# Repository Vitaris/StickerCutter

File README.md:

# StickerCutter Conversion Project

Converting a large format printer to cut stickers

Project Overview

This project aims to repurpose a non-functional large format printer into a sticker cutting machine. The system will be controlled by a Raspberry Pi Pico rp2040 microcontroller board. An optical sensor on the former print head will detect marks around printed stickers, and a blade on the print head, which originally cut the print job after completion, will now cut strips of stickers. The project is written in C and will be released as open source on GitHub.

## Features

- **Mechanical Modifications:** The printer's existing printing head will be adapted to function as a sticker cutting head. This will involve adding an optical sensor to detect markers around printed stickers.
  
- **Software Control:** The Raspberry Pico rp2040 will control the cutting process. The software will interpret the signals from the optical sensor and instruct the cutting blade accordingly.
  
- **Language & Platform:** The project will be implemented in C language for the Raspberry Pico rp2040 microcontroller platform.
  
- **Open Source:** This project will be open source and hosted on GitHub, allowing for collaboration, contributions, and improvements from the community.

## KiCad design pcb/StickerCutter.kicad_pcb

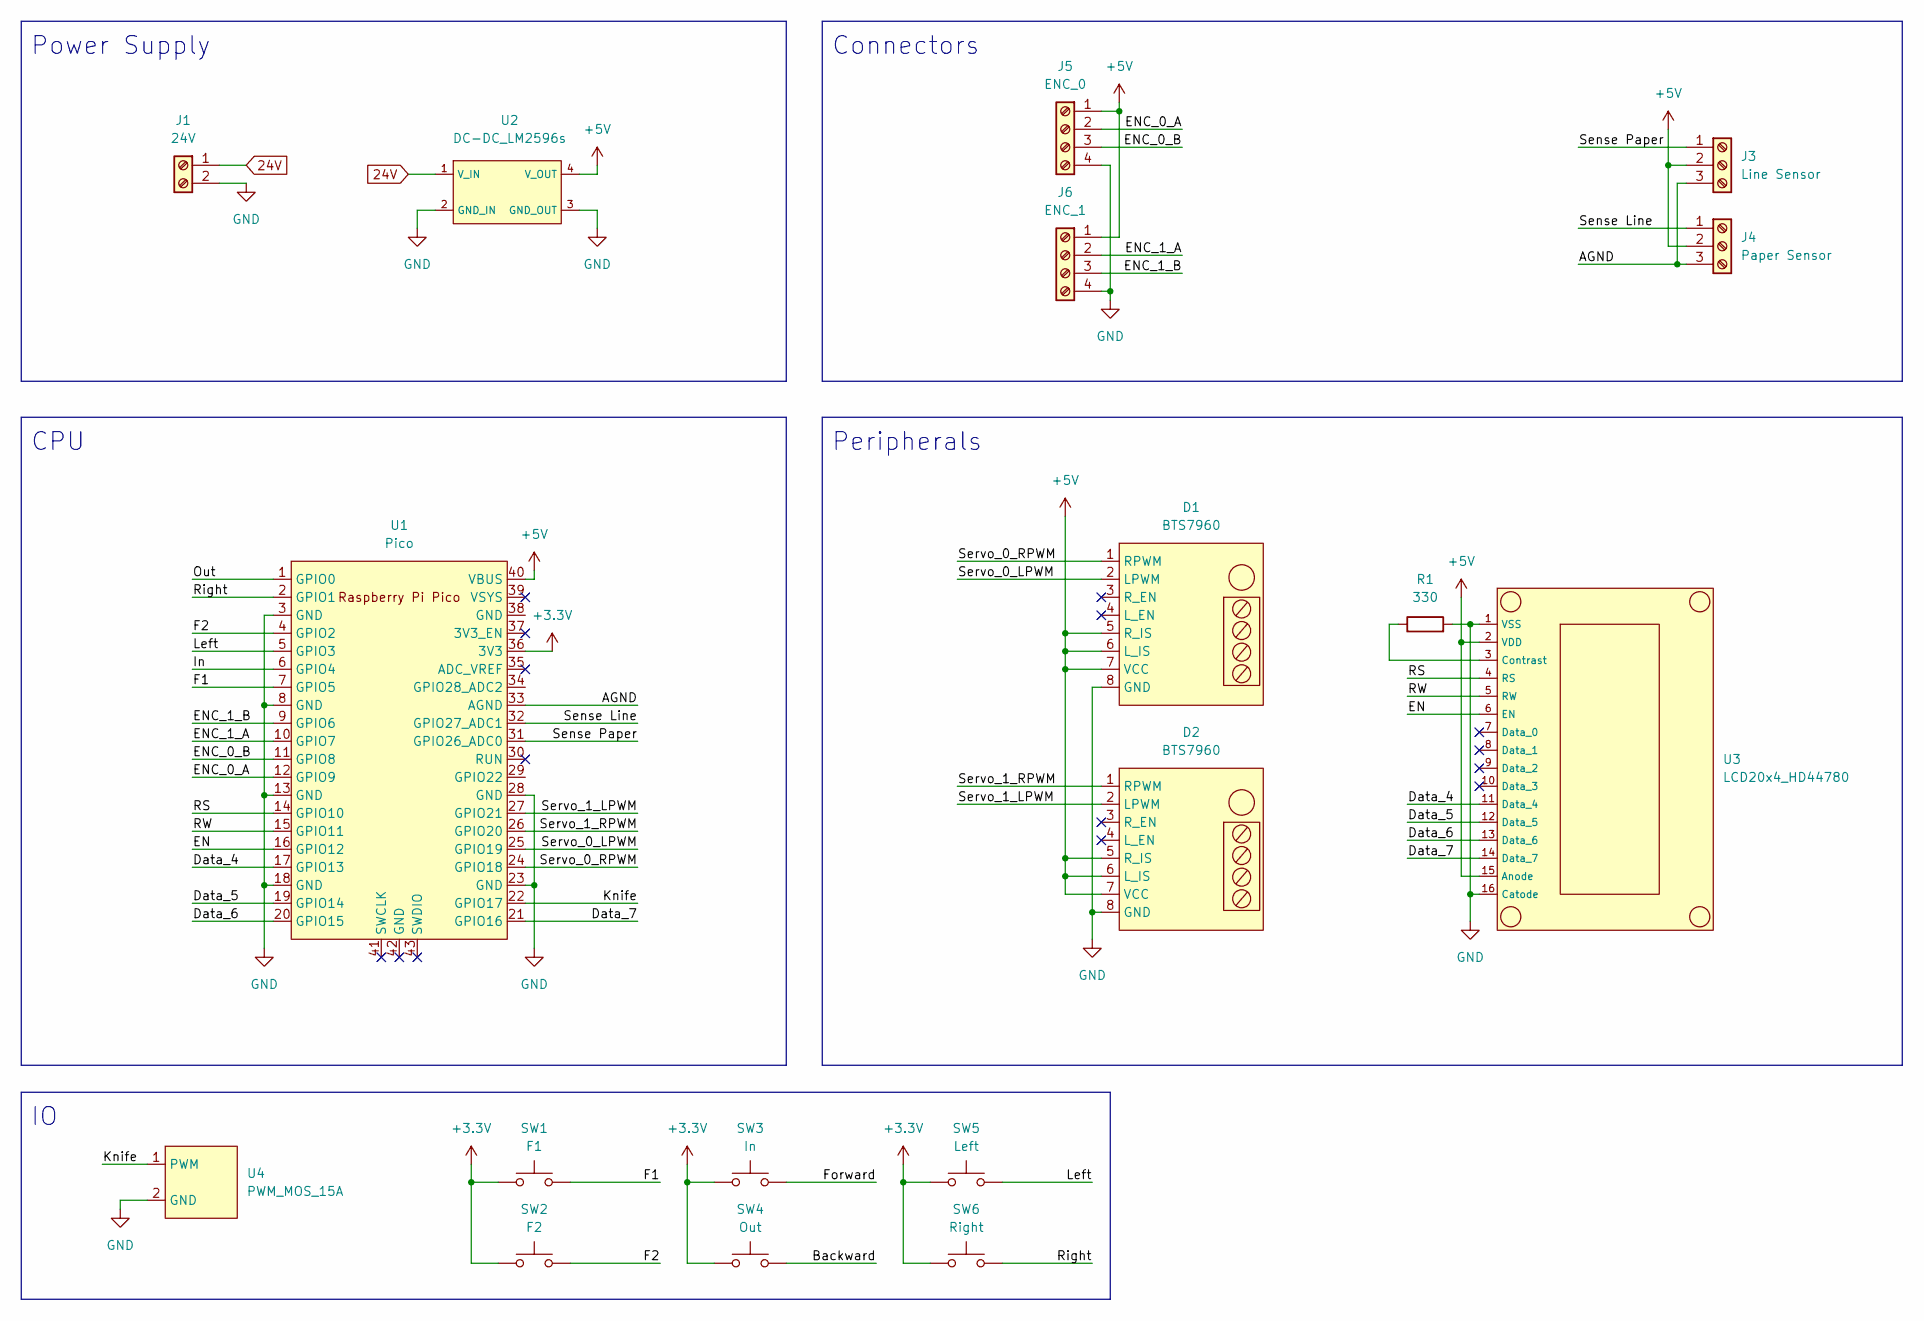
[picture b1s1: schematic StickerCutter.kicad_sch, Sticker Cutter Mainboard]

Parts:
D1, D2: BTS7960
J1: 24V; TerminalBlock_4Ucon_1x02_P3.50mm_Horizontal
J3: Line Sensor; TerminalBlock_4Ucon_1x03_P3.50mm_Horizontal
J4: Paper Sensor; TerminalBlock_4Ucon_1x03_P3.50mm_Horizontal
J5: ENC_0; TerminalBlock_4Ucon_1x04_P3.50mm_Horizontal
J6: ENC_1; TerminalBlock_4Ucon_1x04_P3.50mm_Horizontal
R1: 330; R_2010_5025Metric
SW1: F1; SW_PUSH_6mm
SW2: F2; SW_PUSH_6mm
SW3: In; SW_PUSH_6mm
SW4: Out; SW_PUSH_6mm
SW5: Left; SW_PUSH_6mm
SW6: Right; SW_PUSH_6mm
U1: Pico; RPi_Pico_SMD_TH
U2: DC-DC_LM2596s; LM2596S DC-DC Converter module
U3: LCD20x4_HD44780; HD44780 2004A
U4: PWM_MOS_15A; MOS_PWM_15A

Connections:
24V: J1.1, U2.1 (V_IN)
+3.3V: SW1.1, SW2.1, SW3.1, SW4.1, SW5.1, SW6.1, U1.36 (3V3)
+5V: D1.5 (R_IS), D1.6 (L_IS), D1.7 (VCC), D2.5 (R_IS), D2.6 (L_IS), D2.7 (VCC), J3.2, J4.2, J5.1, J6.1, U1.40 (VBUS), U2.4 (V_OUT), U3.2 (VDD), U3.15 (Anode)
/AGND: J3.3, J4.3, U1.33 (AGND)
/Backward: SW4.2
/Data_4: U1.17 (GPIO13), U3.11 (Data_4)
/Data_5: U1.19 (GPIO14), U3.12 (Data_5)
/Data_6: U1.20 (GPIO15), U3.13 (Data_6)
/Data_7: U1.21 (GPIO16), U3.14 (Data_7)
/EN: U1.16 (GPIO12), U3.6 (EN)
/ENC_0_A: J5.2, U1.12 (GPIO9)
/ENC_0_B: J5.3, U1.11 (GPIO8)
/ENC_1_A: J6.2, U1.10 (GPIO7)
/ENC_1_B: J6.3, U1.9 (GPIO6)
/F1: SW1.2, U1.7 (GPIO5)
/F2: SW2.2, U1.4 (GPIO2)
/Forward: SW3.2
/In: U1.6 (GPIO4)
/Knife: U1.22 (GPIO17), U4.1 (PWM)
/Left: SW5.2, U1.5 (GPIO3)
/Out: U1.1 (GPIO0)
/RS: U1.14 (GPIO10), U3.4 (RS)
/RW: U1.15 (GPIO11), U3.5 (RW)
/Right: SW6.2, U1.2 (GPIO1)
/Sense Line: J4.1, U1.32 (GPIO27_ADC1)
/Sense Paper: J3.1, U1.31 (GPIO26_ADC0)
/Servo_0_LPWM: D1.2 (LPWM), U1.25 (GPIO19)
/Servo_0_RPWM: D1.1 (RPWM), U1.24 (GPIO18)
/Servo_1_LPWM: D2.2 (LPWM), U1.27 (GPIO21)
/Servo_1_RPWM: D2.1 (RPWM), U1.26 (GPIO20)
GND: D1.8 (GND), D2.8 (GND), J1.2, J5.4, J6.4, R1.2, U1.3 (GND), U1.8 (GND), U1.13 (GND), U1.18 (GND), U1.23 (GND), U1.28 (GND), U2.2 (GND_IN), U2.3 (GND_OUT), U3.1 (VSS), U3.16 (Catode), U4.2 (GND)
unnamed: R1.1, U3.3 (Contrast)

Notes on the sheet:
Power Supply
Peripherals
Connectors
CPU

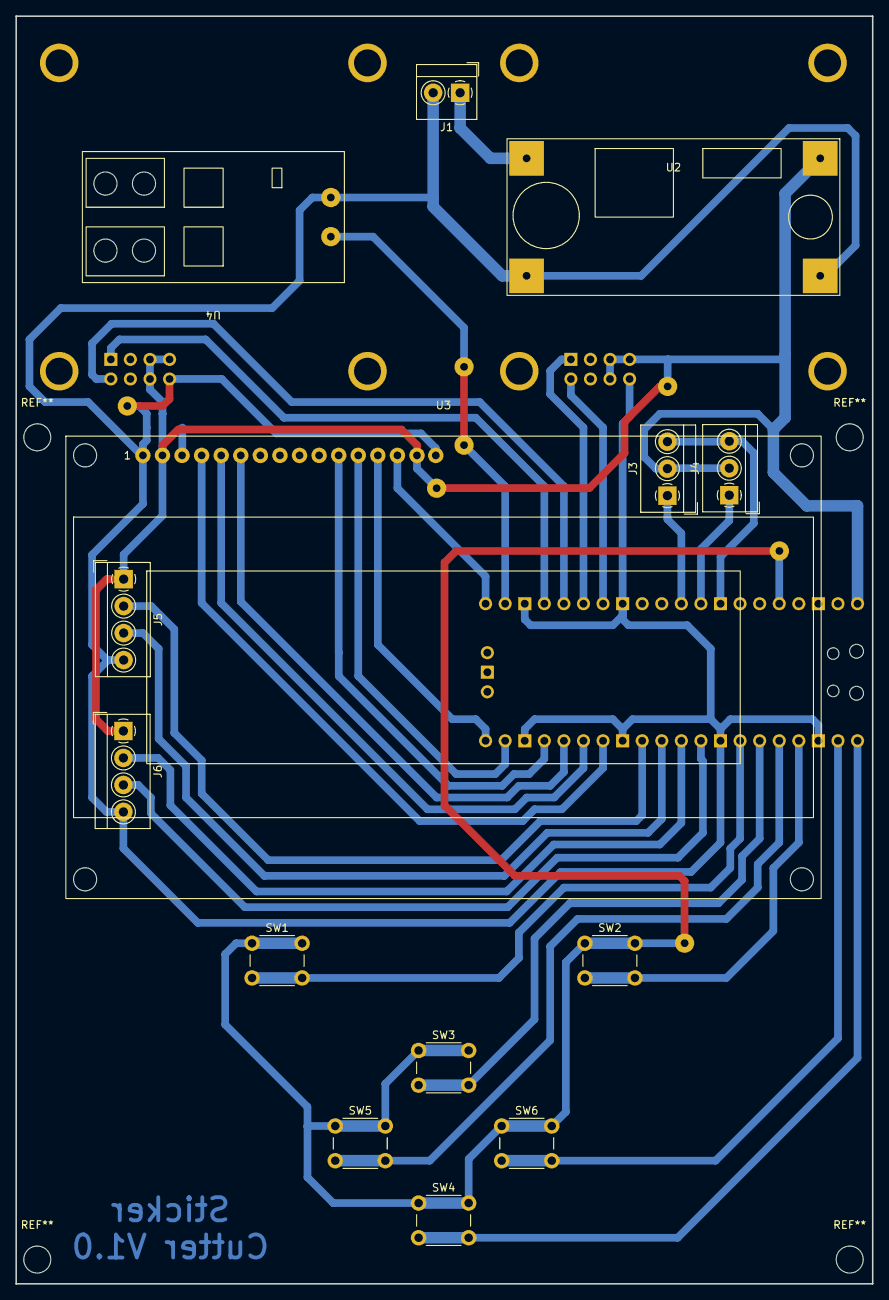
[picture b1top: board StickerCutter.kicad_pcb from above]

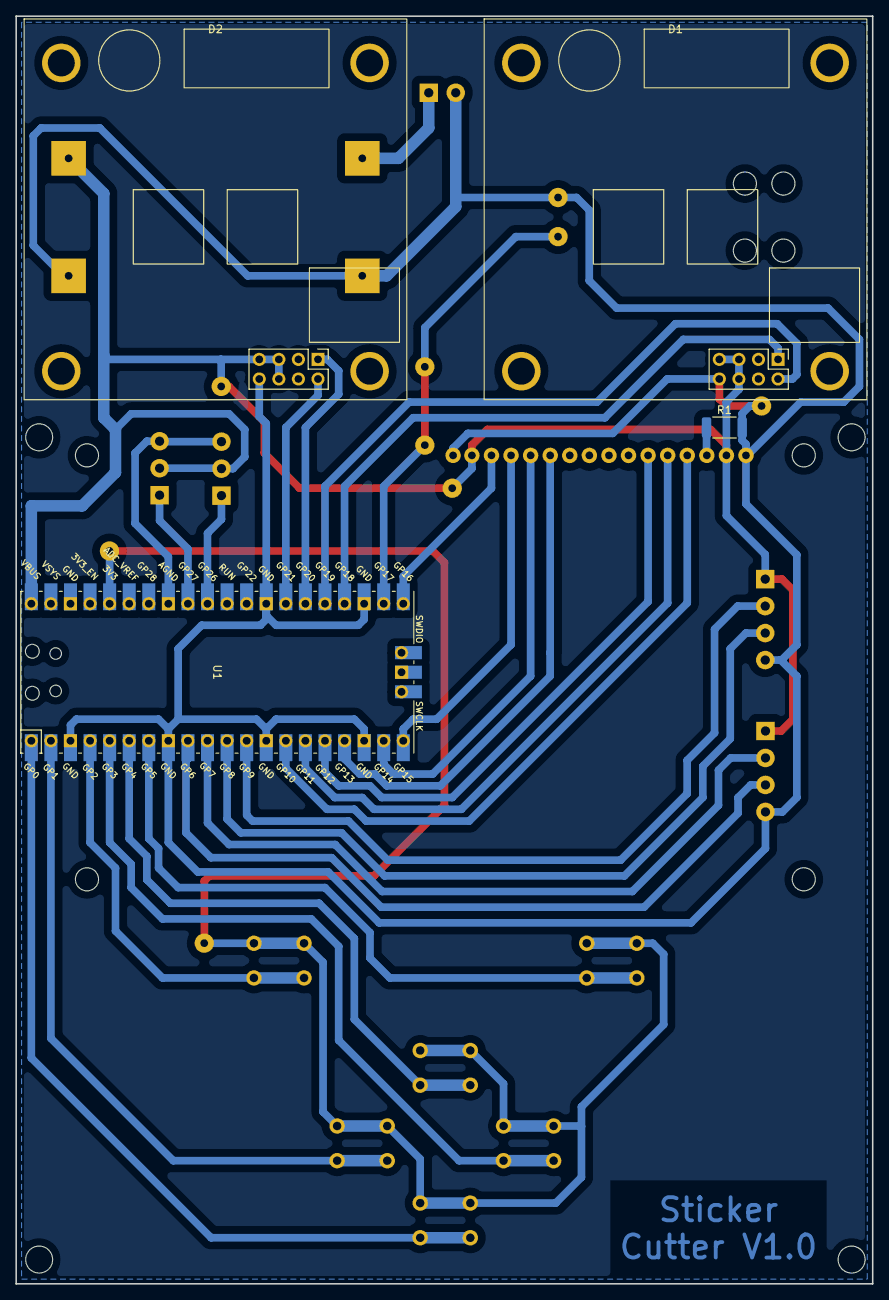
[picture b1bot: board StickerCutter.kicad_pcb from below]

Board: 2 copper layers, 111.1 x 164.5 mm, 18 parts (4 on the bottom side), 28 nets.

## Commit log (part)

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2022-11-25 Fixed problems with PID caused by sleep_ms
2022-11-25 gitignore fixed
2022-11-25 Partially fixed the lcd issue sleep_ms -> busy_wait_ms
2022-11-25 Added servo_pwm files
2022-11-25 Added pos PID
2022-11-26 Some speed ramp testing
2022-11-27 Improved time measurement
2022-11-28 Added positional PID controller
2022-11-29 Added distance computation
2022-12-05 Tunnig pos regulator
2022-12-07 Some tunning
2022-12-09 Best PID values
2022-12-09 Foundation for positional controller
2022-12-11 Added position controller
2023-01-02 Added python plotter
    Not working yet
2023-01-02 Almost empty breadboard
2023-01-13 Added servo_motor
2023-01-14 Added multicore LCD support
2023-02-04 PCB initial commit
    First verison of board
2023-02-06 Fixed forgotten routes
2023-02-24 Added Ant lcd lib
2023-02-25 Two servos working
2023-02-27 Added buttons, improved manual mode
2023-02-27 Updated encoder colors desc
2023-02-28 Added test lines
2023-04-18 Some servo changes
2023-04-18 Changed pin mappings
2023-04-18 Feeder func prototypes
2023-04-20 Added buttons
2023-04-26 Added feeder feature
2023-05-13 Added machine controller, changes in lcd
2023-05-20 Preparation for a demo
2023-05-20 Deleted unused declarations
2023-06-17 Added mark_detector
2023-06-17 sync
2023-06-17 Moved pwm chans to fit pwm hw pairs in RP2040
2023-06-17 Deleted temporary fix of pwm channels deleted unused code in pid
2023-06-19 Added malloc to create datastructures
2023-06-19 mark_probe
2023-06-29 minor changes
2024-04-12 Add some basics
2024-04-21 some refactor
2024-04-21 Update desc
2024-04-24 Generalize some part of code
2024-04-24 merged changes from old stash
2024-04-24 Add error handling
2024-05-05 Add following error handling
2024-05-05 Add buttons for state handling
2024-05-05 Add correct condition for button
2024-06-03 Jog position
2024-06-03 Base fo robust pos controler
2024-06-04 improve ramp and continues movement
2024-06-12 Pos controller changes
2024-06-15 Position controler improvements
2024-06-15 Pos controller optimizations
2024-06-16 machine state handling, minor code optimization
2024-06-19 Manual mode improvement
2024-07-11 Move staff from main to machine
2024-07-12 lcd and modes improvements
2024-07-13 Added state machine
2024-07-13 Early automat mode
2024-07-14 Add state machine to servo controler
2024-07-14 Add PID Error
2024-07-14 Implement PID error and servo zeroing
2024-07-17 Changed periodic timer which executes exactly every 1ms and removed cycle time
2024-07-17 Add delay for goto
2024-07-18 Change reach position evaluation to speed
2024-07-18 Add cutting algorithm
2024-07-19 Add mark detector to machine
2024-08-03 Add simulation for Mark detector
2024-08-03 Clearing
2024-08-03 Detector calibration work
2024-08-03 Add delayed version of servo_goto
2024-09-05 Set UINT32_MAX to delay for sign there is no delay
2024-09-05 Add the roll of paper after cutting
2024-11-02 PID and speed tunning
2024-11-02 Offline changes from train
2024-11-02 Fix merge errors
2024-11-02 Scale motors
2024-11-07 Samples average calculate
2024-11-14 attempt to get sync arrays of paper whiteness and feeder position
2024-11-20 Line detector proto
2024-11-24 Line detection improvement
2024-12-11 Automatic homing
2024-12-12 Automatic homing wip
2024-12-15 Home sequence almost done
2024-12-16 Add limits to servo manual handling
2024-12-16 Remove speed from lcd
2024-12-16 machine improvements
2025-01-10 Add some new enum for state machine
2025-01-18 Add descriptive comments
2025-01-18 Add display handling file
2025-01-18 Split manual mode from main machine file, make machine structure global
2025-01-18 Add new files to CMakelist
2025-01-18 Add missing descripive comment
2025-01-18 Deleted files
2025-01-19 Revert changes in lcd variable updating
2025-01-29 Add changes
2025-01-31 Implement homing state and update machine initialization
2025-01-31 Refactor paper presence detection and add absence check
2025-01-31 Refactor paper presence functions to void presence functions
2025-01-31 Fix spelling errors in homing state references
2025-01-31 Refactor homing state management and enhance absence detection
2025-01-31 Refactor detector handling to use a global instance and improve initialization
2025-01-31 Enhance documentation for detector state machine and error codes
2025-02-03 Enhance documentation for manual and homing operation modes
2025-02-03 Add automatic mode source file to CMake build configuration
2025-02-03 Add automatic mode functionality and parameter setting sequence
2025-02-04 Minor bugfixes
2025-02-06 Add flag "Nominal speed reached"
2025-02-06 Refactor mark detector logic and remove unused state machine code
2025-02-06 Implement automatic mode state transitions and enhance mark detection logic
2025-02-06 Refactor detector initialization and update error handling in automatic mode
2025-02-08 Refactor mark detection function and introduce moving average filter for improved accuracy
2025-02-09 Update servo speed for mark detection and refactor range detection logic
2025-02-10 Enhance automatic mode with mark monitoring
2025-02-12 Refactor automatic mode state handling and enhance mark detection logic
2025-02-12 Rename state_text to state_text_1 for consistency in display handling
2025-02-12 Add HALF_SECOND_DELAY constant for improved timing control
2025-02-13 Ensure knife is raised when not in AUTOMAT state for safety
2025-02-13 Enhance automatic mode with additional cut sections and improved mark handling
2025-02-13 temporar fix
2025-02-14 Adjust automatic speed constants for improved performance
2025-02-14 Adjust paper position values for manual mode
2025-02-14 Update sensor knife offset definitions for improved accuracy
2025-02-14 Refactor automatic mode to improve mark handling and cutting sequence
2025-02-15 Enhance automatic mode state machine with detailed comments and improved mark detection logic
2025-02-15 Add functionality to stop knife between marks in automatic mode
2025-02-19 Enhance automatic mode with improved mark distance validation and error handling
2025-02-19 Move unnecessary declarations out of the header file and into c
2025-02-20 Refactor code structure for better readability and maintainability
2025-02-20 Improve and move several function declarations
2025-02-20 Remove unnecessary blank lines in mark_detector.h
2025-02-20 Refactor automatic and manual mode files to improve variable visibility and enhance documentation
2025-02-21 Refactor mark_detector to use local variable for reflectivity and simplify void presence checks
2025-02-22 Refactor manual and automatic mode files to remove detector dependency and improve function clarity
2025-02-22 Remove current_reflectivity variable
2025-02-22 Refactor machine controller to remove unused variables and improve function clarity; add activate_failure_state function for better error handling
2025-02-22 Remove unused old_cycle_time variable
2025-02-22 Remove HOMING_START state from homing seq
2025-02-22 Refactor error handling in machine_compute to use activate_failure_state function
2025-02-22 Refactor init_detector function parameters for clarity and safety
2025-02-22 Refactor servo functions for consistency and clarity
2025-02-22 Refactor servo motor functions: remove unused stop handling and add braking distance calculation
2025-02-22 Refactor detector structure: encapsulate state and improve variable management
2025-02-22 Refactor detector logic: enhance spike detection and long-term averaging
2025-02-22 Enhance documentation: add detailed comments for long-term average update and spike area calculation
2025-02-22 Refactor detector functions: reorganize spike area calculation and long-term average update for clarity and maintainability
2025-02-23 Speed constants: rename and adjust speed definitions for clarity and improved functionality
2025-02-23 Update servo speeds for automatic mode: adjust speed constants
2025-02-23 Increase memory size and adjust threshold constants for improved spike detection
2025-03-16 Remove parameter setting state functionality from manual mode
2025-03-16 Refactor automatic mode: simplify servo positions for cutting edges and remove parameter handling state
2025-03-17 Remove descriptive comments for better readability
2025-03-19 Refactor servo_motor structure: simplify type definition and update function signatures for pointer usage
2025-03-19 Refactor machine controller: update servo pointers for improved position handling
2025-03-19 Refactor sticker cutter: replace direct servo position access with getter function
2025-03-19 Replace direct servo state checks with dedicated functions
2025-03-19 Remove unused function declaration
2025-03-19 Add youtube thumbnail pic
2025-03-19 Remove unused variables and update function signatures for const correctness
2025-03-20 Refactor PID controller implementation to use a new data structure and improve error handling
2025-03-23 Refactor button implementation to improve state management and debouncing logic
2025-03-23 Refactor LCD library to use pointer-based structure
2025-03-23 Refactor display_20x4 implementation to use a pointer-based structure
2025-03-23 Refactor servo motor implementation
2025-03-29 Remove display_20x4 implementation and update CMakeLists.txt
2025-03-29 Refactor mark_detector.c to use static constants for configuration values
2025-03-29 Refactor sticker_cutter.c to replace display_20x4 with devices structure for LCD handling
2025-03-29 Refactor machine mode headers and implementation to use pointer-based structures for devices
2025-04-04 Add functions to reset and check paper mark positions in automatic mode
2025-04-04 Separate paper mark positions, left and right
2025-04-04 Add manual mode functionality for setting paper mark positions
2025-04-05 Add function to check if nominal speed is reached for servo motor
2025-04-05 Add slow version for manual movement function
2025-04-05 Add debug values for paper positions
2025-04-05 change incorrect function call and refactor a bit mark found logic
2025-04-25 Add state text 2
2025-04-25 Print out measured sticker heigth to lcd
2025-04-25 Remove everything related left mark
2025-04-25 Remove unused rotary encoder PIO program
2025-04-25 Add BOM
2025-04-25 Updated BOM table
2025-04-25 Refactor state text handling and update paper right mark position
2025-06-06 Add intro screen
2025-06-06 Reset mark position when manual
2025-06-08 Remove debug setting
2025-06-12 Update bom
2025-06-12 Rename servo motors to more descriptive names
2025-06-12 fixed setting of last_stop_position value
2025-06-12 Updated version number
2026-01-03 Add changes from pico extension
2026-01-03 Fix parameter size in servo_create function signature
2026-01-03 Fix time type in button structure to uint64_t for consistency
2026-01-03 Add missing includes for hardware and quadrature encoder
2026-01-03 Add missing include for quadrature encoder in sticker_cutter.c
2026-01-03 Change type declaration for constants
2026-01-18 Add file
2026-01-18 Refactor constants to #define and change type declarations for consistency
2026-01-18 Make lcd_refresh volatile to ensure proper synchronization in multi-core environment
2026-01-19 Print debug reflectivity data
2026-01-19 Reflectivity data files
